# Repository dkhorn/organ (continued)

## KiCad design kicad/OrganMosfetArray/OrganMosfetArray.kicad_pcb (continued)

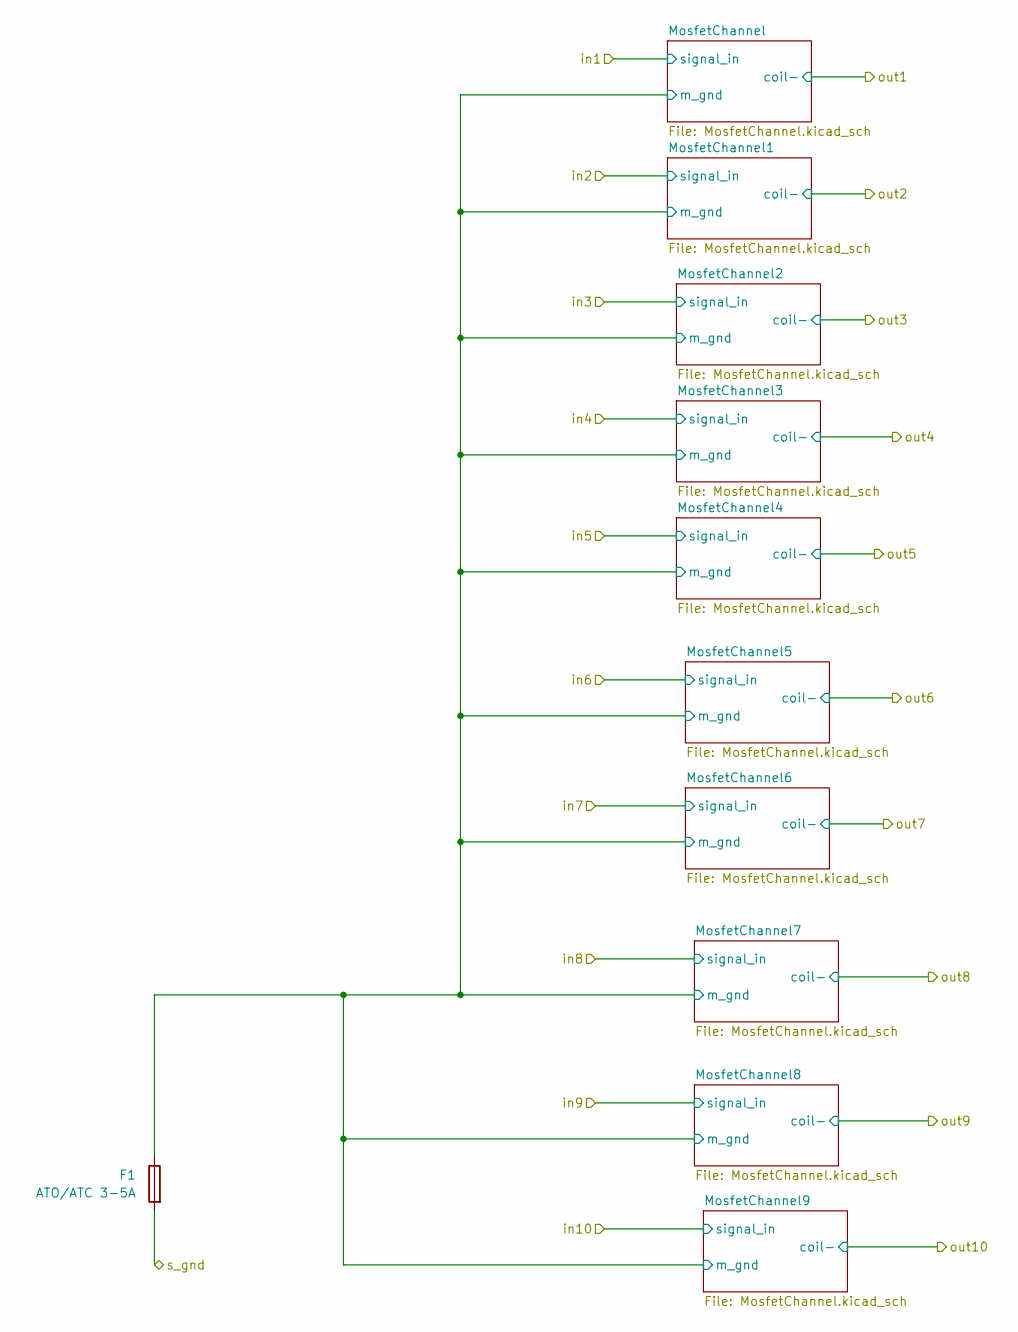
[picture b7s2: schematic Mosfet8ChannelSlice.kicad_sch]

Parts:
F1: ATO/ATC 3-5A; AliExpressFuseHolder

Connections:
/Mosfet8ChannelSlice/MosfetChannel/m_gnd: F1.1; also elsewhere on the board
GND: F1.2; also elsewhere on the board

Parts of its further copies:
F2, F3, F4, F5: ATO/ATC 3-5A; AliExpressFuseHolder

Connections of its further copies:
/Mosfet8ChannelSlice1/MosfetChannel/m_gnd: F2.1; also elsewhere on the board
/Mosfet8ChannelSlice2/MosfetChannel/m_gnd: F3.1; also elsewhere on the board
/Mosfet8ChannelSlice3/MosfetChannel/m_gnd: F4.1; also elsewhere on the board
/Mosfet8ChannelSlice4/MosfetChannel/m_gnd: F5.1; also elsewhere on the board
GND: F2.2, F3.2, F4.2, F5.2; also elsewhere on the board

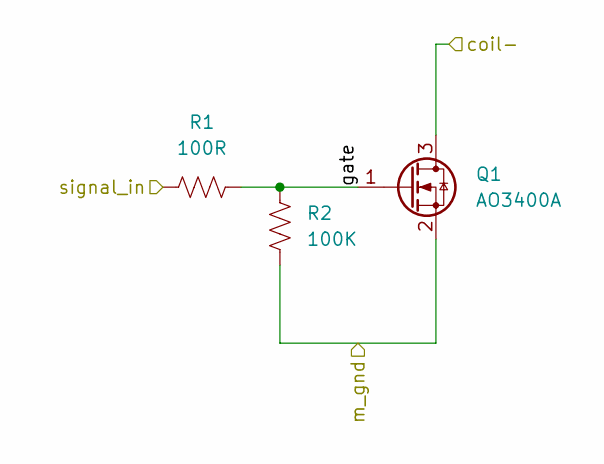
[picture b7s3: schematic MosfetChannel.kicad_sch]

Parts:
Q1: AO3400A; SOT-23
R1: 100R; R_0603_1608Metric
R2: 100K; R_0603_1608Metric

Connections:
/Mosfet8ChannelSlice/MosfetChannel/gate: Q1.1 (G), R1.2, R2.1
/Mosfet8ChannelSlice/MosfetChannel/m_gnd: Q1.2 (S), R2.2; also elsewhere on the board
/Mosfet8ChannelSlice/in1: R1.1; also elsewhere on the board
/Mosfet8ChannelSlice/out1: Q1.3 (D); also elsewhere on the board

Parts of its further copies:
Q2, Q3, Q4, Q5, Q6, Q7, Q8, Q9, Q10, Q11, Q12, Q13, Q14, Q15, Q16, Q17, Q18, Q19, Q20, Q21, Q22, Q23, Q24, Q25, Q26, Q27, Q28, Q29, Q30, Q31, Q32, Q33, Q34, Q35, Q36, Q37, Q38, Q39, Q40, Q41, Q42, Q43, Q44, Q45, Q46, Q47, Q48, Q49, Q50: AO3400A; SOT-23
R3, R5, R7, R9, R11, R13, R15, R17, R19, R21, R23, R25, R27, R29, R31, R33, R35, R37, R39, R41, R43, R45, R47, R49, R51, R53, R55, R57, R59, R61, R63, R65, R67, R69, R71, R73, R75, R77, R79, R81, R83, R85, R87, R89, R91, R93, R95, R97, R99: 100R; R_0603_1608Metric
R4, R6, R8, R10, R12, R14, R16, R18, R20, R22, R24, R26, R28, R30, R32, R34, R36, R38, R40, R42, R44, R46, R48, R50, R52, R54, R56, R58, R60, R62, R64, R66, R68, R70, R72, R74, R76, R78, R80, R82, R84, R86, R88, R90, R92, R94, R96, R98, R100: 100K; R_0603_1608Metric

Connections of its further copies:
/Mosfet8ChannelSlice1/MosfetChannel1/gate: Q11.1 (G), R21.2, R22.1
/Mosfet8ChannelSlice1/MosfetChannel2/gate: Q10.1 (G), R19.2, R20.1
/Mosfet8ChannelSlice1/MosfetChannel3/gate: Q9.1 (G), R17.2, R18.1
/Mosfet8ChannelSlice1/MosfetChannel4/gate: Q14.1 (G), R27.2, R28.1
/Mosfet8ChannelSlice1/MosfetChannel5/gate: Q12.1 (G), R23.2, R24.1
/Mosfet8ChannelSlice1/MosfetChannel6/gate: Q15.1 (G), R29.2, R30.1
/Mosfet8ChannelSlice1/MosfetChannel7/gate: Q16.1 (G), R31.2, R32.1
/Mosfet8ChannelSlice1/MosfetChannel8/gate: Q17.1 (G), R33.2, R34.1
/Mosfet8ChannelSlice1/MosfetChannel9/gate: Q18.1 (G), R35.2, R36.1
/Mosfet8ChannelSlice1/MosfetChannel/gate: Q13.1 (G), R25.2, R26.1
/Mosfet8ChannelSlice1/MosfetChannel/m_gnd: Q9.2 (S), Q10.2 (S), Q11.2 (S), Q12.2 (S), Q13.2 (S), Q14.2 (S), Q15.2 (S), Q16.2 (S), Q17.2 (S), Q18.2 (S), R18.2, R20.2, R22.2, R24.2, R26.2, R28.2, R30.2, R32.2, R34.2, R36.2; also elsewhere on the board
/Mosfet8ChannelSlice1/in1: R25.1; also elsewhere on the board
/Mosfet8ChannelSlice1/in2: R21.1; also elsewhere on the board
/Mosfet8ChannelSlice1/in3: R19.1; also elsewhere on the board
/Mosfet8ChannelSlice1/in4: R17.1; also elsewhere on the board
/Mosfet8ChannelSlice1/in5: R27.1; also elsewhere on the board
/Mosfet8ChannelSlice1/in6: R23.1; also elsewhere on the board
/Mosfet8ChannelSlice1/in7: R29.1; also elsewhere on the board
/Mosfet8ChannelSlice1/in8: R31.1; also elsewhere on the board
/Mosfet8ChannelSlice1/in9: R33.1; also elsewhere on the board
/Mosfet8ChannelSlice1/in10: R35.1; also elsewhere on the board
/Mosfet8ChannelSlice1/out1: Q13.3 (D); also elsewhere on the board
/Mosfet8ChannelSlice1/out2: Q11.3 (D); also elsewhere on the board
/Mosfet8ChannelSlice1/out3: Q10.3 (D); also elsewhere on the board
/Mosfet8ChannelSlice1/out4: Q9.3 (D); also elsewhere on the board
/Mosfet8ChannelSlice1/out5: Q14.3 (D); also elsewhere on the board
/Mosfet8ChannelSlice1/out6: Q12.3 (D); also elsewhere on the board
/Mosfet8ChannelSlice1/out7: Q15.3 (D); also elsewhere on the board
/Mosfet8ChannelSlice1/out8: Q16.3 (D); also elsewhere on the board
/Mosfet8ChannelSlice1/out9: Q17.3 (D); also elsewhere on the board
/Mosfet8ChannelSlice1/out10: Q18.3 (D); also elsewhere on the board
/Mosfet8ChannelSlice2/MosfetChannel1/gate: Q21.1 (G), R41.2, R42.1
/Mosfet8ChannelSlice2/MosfetChannel2/gate: Q20.1 (G), R39.2, R40.1
/Mosfet8ChannelSlice2/MosfetChannel3/gate: Q19.1 (G), R37.2, R38.1
/Mosfet8ChannelSlice2/MosfetChannel4/gate: Q24.1 (G), R47.2, R48.1
/Mosfet8ChannelSlice2/MosfetChannel5/gate: Q22.1 (G), R43.2, R44.1
/Mosfet8ChannelSlice2/MosfetChannel6/gate: Q25.1 (G), R49.2, R50.1
/Mosfet8ChannelSlice2/MosfetChannel7/gate: Q26.1 (G), R51.2, R52.1
/Mosfet8ChannelSlice2/MosfetChannel8/gate: Q27.1 (G), R53.2, R54.1
/Mosfet8ChannelSlice2/MosfetChannel9/gate: Q28.1 (G), R55.2, R56.1
/Mosfet8ChannelSlice2/MosfetChannel/gate: Q23.1 (G), R45.2, R46.1
/Mosfet8ChannelSlice2/MosfetChannel/m_gnd: Q19.2 (S), Q20.2 (S), Q21.2 (S), Q22.2 (S), Q23.2 (S), Q24.2 (S), Q25.2 (S), Q26.2 (S), Q27.2 (S), Q28.2 (S), R38.2, R40.2, R42.2, R44.2, R46.2, R48.2, R50.2, R52.2, R54.2, R56.2; also elsewhere on the board
/Mosfet8ChannelSlice2/in1: R45.1; also elsewhere on the board
/Mosfet8ChannelSlice2/in2: R41.1; also elsewhere on the board
/Mosfet8ChannelSlice2/in3: R39.1; also elsewhere on the board
/Mosfet8ChannelSlice2/in4: R37.1; also elsewhere on the board
/Mosfet8ChannelSlice2/in5: R47.1; also elsewhere on the board
/Mosfet8ChannelSlice2/in6: R43.1; also elsewhere on the board
/Mosfet8ChannelSlice2/in7: R49.1; also elsewhere on the board
/Mosfet8ChannelSlice2/in8: R51.1; also elsewhere on the board
/Mosfet8ChannelSlice2/in9: R53.1; also elsewhere on the board
/Mosfet8ChannelSlice2/in10: R55.1; also elsewhere on the board
/Mosfet8ChannelSlice2/out1: Q23.3 (D); also elsewhere on the board
/Mosfet8ChannelSlice2/out2: Q21.3 (D); also elsewhere on the board
/Mosfet8ChannelSlice2/out3: Q20.3 (D); also elsewhere on the board
/Mosfet8ChannelSlice2/out4: Q19.3 (D); also elsewhere on the board
/Mosfet8ChannelSlice2/out5: Q24.3 (D); also elsewhere on the board
/Mosfet8ChannelSlice2/out6: Q22.3 (D); also elsewhere on the board
/Mosfet8ChannelSlice2/out7: Q25.3 (D); also elsewhere on the board
/Mosfet8ChannelSlice2/out8: Q26.3 (D); also elsewhere on the board
/Mosfet8ChannelSlice2/out9: Q27.3 (D); also elsewhere on the board
/Mosfet8ChannelSlice2/out10: Q28.3 (D); also elsewhere on the board
/Mosfet8ChannelSlice3/MosfetChannel1/gate: Q31.1 (G), R61.2, R62.1
/Mosfet8ChannelSlice3/MosfetChannel2/gate: Q30.1 (G), R59.2, R60.1
/Mosfet8ChannelSlice3/MosfetChannel3/gate: Q29.1 (G), R57.2, R58.1
/Mosfet8ChannelSlice3/MosfetChannel4/gate: Q34.1 (G), R67.2, R68.1
/Mosfet8ChannelSlice3/MosfetChannel5/gate: Q32.1 (G), R63.2, R64.1
/Mosfet8ChannelSlice3/MosfetChannel6/gate: Q35.1 (G), R69.2, R70.1
/Mosfet8ChannelSlice3/MosfetChannel7/gate: Q36.1 (G), R71.2, R72.1
/Mosfet8ChannelSlice3/MosfetChannel8/gate: Q37.1 (G), R73.2, R74.1
/Mosfet8ChannelSlice3/MosfetChannel9/gate: Q38.1 (G), R75.2, R76.1
/Mosfet8ChannelSlice3/MosfetChannel/gate: Q33.1 (G), R65.2, R66.1
/Mosfet8ChannelSlice3/MosfetChannel/m_gnd: Q29.2 (S), Q30.2 (S), Q31.2 (S), Q32.2 (S), Q33.2 (S), Q34.2 (S), Q35.2 (S), Q36.2 (S), Q37.2 (S), Q38.2 (S), R58.2, R60.2, R62.2, R64.2, R66.2, R68.2, R70.2, R72.2, R74.2, R76.2; also elsewhere on the board
/Mosfet8ChannelSlice3/in1: R65.1; also elsewhere on the board
/Mosfet8ChannelSlice3/in2: R61.1; also elsewhere on the board
/Mosfet8ChannelSlice3/in3: R59.1; also elsewhere on the board
/Mosfet8ChannelSlice3/in4: R57.1; also elsewhere on the board
/Mosfet8ChannelSlice3/in5: R67.1; also elsewhere on the board
/Mosfet8ChannelSlice3/in6: R63.1; also elsewhere on the board
/Mosfet8ChannelSlice3/in7: R69.1; also elsewhere on the board
/Mosfet8ChannelSlice3/in8: R71.1; also elsewhere on the board
/Mosfet8ChannelSlice3/in9: R73.1; also elsewhere on the board
/Mosfet8ChannelSlice3/in10: R75.1; also elsewhere on the board
/Mosfet8ChannelSlice3/out1: Q33.3 (D); also elsewhere on the board
/Mosfet8ChannelSlice3/out2: Q31.3 (D); also elsewhere on the board
/Mosfet8ChannelSlice3/out3: Q30.3 (D); also elsewhere on the board
/Mosfet8ChannelSlice3/out4: Q29.3 (D); also elsewhere on the board
/Mosfet8ChannelSlice3/out5: Q34.3 (D); also elsewhere on the board
/Mosfet8ChannelSlice3/out6: Q32.3 (D); also elsewhere on the board
/Mosfet8ChannelSlice3/out7: Q35.3 (D); also elsewhere on the board
/Mosfet8ChannelSlice3/out8: Q36.3 (D); also elsewhere on the board
/Mosfet8ChannelSlice3/out9: Q37.3 (D); also elsewhere on the board
/Mosfet8ChannelSlice3/out10: Q38.3 (D); also elsewhere on the board
/Mosfet8ChannelSlice4/MosfetChannel1/gate: Q41.1 (G), R81.2, R82.1
/Mosfet8ChannelSlice4/MosfetChannel2/gate: Q40.1 (G), R79.2, R80.1
/Mosfet8ChannelSlice4/MosfetChannel3/gate: Q39.1 (G), R77.2, R78.1
/Mosfet8ChannelSlice4/MosfetChannel4/gate: Q44.1 (G), R87.2, R88.1
/Mosfet8ChannelSlice4/MosfetChannel5/gate: Q42.1 (G), R83.2, R84.1
/Mosfet8ChannelSlice4/MosfetChannel6/gate: Q45.1 (G), R89.2, R90.1
/Mosfet8ChannelSlice4/MosfetChannel7/gate: Q46.1 (G), R91.2, R92.1
/Mosfet8ChannelSlice4/MosfetChannel8/gate: Q47.1 (G), R93.2, R94.1
/Mosfet8ChannelSlice4/MosfetChannel9/gate: Q48.1 (G), R95.2, R96.1
/Mosfet8ChannelSlice4/MosfetChannel/gate: Q43.1 (G), R85.2, R86.1
/Mosfet8ChannelSlice4/MosfetChannel/m_gnd: Q39.2 (S), Q40.2 (S), Q41.2 (S), Q42.2 (S), Q43.2 (S), Q44.2 (S), Q45.2 (S), Q46.2 (S), Q47.2 (S), Q48.2 (S), R78.2, R80.2, R82.2, R84.2, R86.2, R88.2, R90.2, R92.2, R94.2, R96.2; also elsewhere on the board
/Mosfet8ChannelSlice4/in1: R85.1; also elsewhere on the board
/Mosfet8ChannelSlice4/in2: R81.1; also elsewhere on the board
/Mosfet8ChannelSlice4/in3: R79.1; also elsewhere on the board
/Mosfet8ChannelSlice4/in4: R77.1; also elsewhere on the board
/Mosfet8ChannelSlice4/in5: R87.1; also elsewhere on the board
/Mosfet8ChannelSlice4/in6: R83.1; also elsewhere on the board
/Mosfet8ChannelSlice4/in7: R89.1; also elsewhere on the board
/Mosfet8ChannelSlice4/in8: R91.1; also elsewhere on the board
/Mosfet8ChannelSlice4/in9: R93.1; also elsewhere on the board
/Mosfet8ChannelSlice4/in10: R95.1; also elsewhere on the board
/Mosfet8ChannelSlice4/out1: Q43.3 (D); also elsewhere on the board
/Mosfet8ChannelSlice4/out2: Q41.3 (D); also elsewhere on the board
/Mosfet8ChannelSlice4/out3: Q40.3 (D); also elsewhere on the board
/Mosfet8ChannelSlice4/out4: Q39.3 (D); also elsewhere on the board
/Mosfet8ChannelSlice4/out5: Q44.3 (D); also elsewhere on the board
/Mosfet8ChannelSlice4/out6: Q42.3 (D); also elsewhere on the board
/Mosfet8ChannelSlice4/out7: Q45.3 (D); also elsewhere on the board
/Mosfet8ChannelSlice4/out8: Q46.3 (D); also elsewhere on the board
/Mosfet8ChannelSlice4/out9: Q47.3 (D); also elsewhere on the board
/Mosfet8ChannelSlice4/out10: Q48.3 (D); also elsewhere on the board
/Mosfet8ChannelSlice/MosfetChannel1/gate: Q2.1 (G), R3.2, R4.1
/Mosfet8ChannelSlice/MosfetChannel2/gate: Q3.1 (G), R5.2, R6.1
/Mosfet8ChannelSlice/MosfetChannel3/gate: Q4.1 (G), R7.2, R8.1
/Mosfet8ChannelSlice/MosfetChannel4/gate: Q5.1 (G), R9.2, R10.1
/Mosfet8ChannelSlice/MosfetChannel5/gate: Q6.1 (G), R11.2, R12.1
/Mosfet8ChannelSlice/MosfetChannel6/gate: Q7.1 (G), R13.2, R14.1
/Mosfet8ChannelSlice/MosfetChannel7/gate: Q8.1 (G), R15.2, R16.1
/Mosfet8ChannelSlice/MosfetChannel8/gate: Q49.1 (G), R97.2, R98.1
/Mosfet8ChannelSlice/MosfetChannel9/gate: Q50.1 (G), R99.2, R100.1
/Mosfet8ChannelSlice/MosfetChannel/m_gnd: Q2.2 (S), Q3.2 (S), Q4.2 (S), Q5.2 (S), Q6.2 (S), Q7.2 (S), Q8.2 (S), Q49.2 (S), Q50.2 (S), R4.2, R6.2, R8.2, R10.2, R12.2, R14.2, R16.2, R98.2, R100.2; also elsewhere on the board
/Mosfet8ChannelSlice/in2: R3.1; also elsewhere on the board
/Mosfet8ChannelSlice/in3: R5.1; also elsewhere on the board
/Mosfet8ChannelSlice/in4: R7.1; also elsewhere on the board
/Mosfet8ChannelSlice/in5: R9.1; also elsewhere on the board
/Mosfet8ChannelSlice/in6: R11.1; also elsewhere on the board
/Mosfet8ChannelSlice/in7: R13.1; also elsewhere on the board
/Mosfet8ChannelSlice/in8: R15.1; also elsewhere on the board
/Mosfet8ChannelSlice/in9: R97.1; also elsewhere on the board
/Mosfet8ChannelSlice/in10: R99.1; also elsewhere on the board
/Mosfet8ChannelSlice/out2: Q2.3 (D); also elsewhere on the board
/Mosfet8ChannelSlice/out3: Q3.3 (D); also elsewhere on the board
/Mosfet8ChannelSlice/out4: Q4.3 (D); also elsewhere on the board
/Mosfet8ChannelSlice/out5: Q5.3 (D); also elsewhere on the board
/Mosfet8ChannelSlice/out6: Q6.3 (D); also elsewhere on the board
/Mosfet8ChannelSlice/out7: Q7.3 (D); also elsewhere on the board
/Mosfet8ChannelSlice/out8: Q8.3 (D); also elsewhere on the board
/Mosfet8ChannelSlice/out9: Q49.3 (D); also elsewhere on the board
/Mosfet8ChannelSlice/out10: Q50.3 (D); also elsewhere on the board

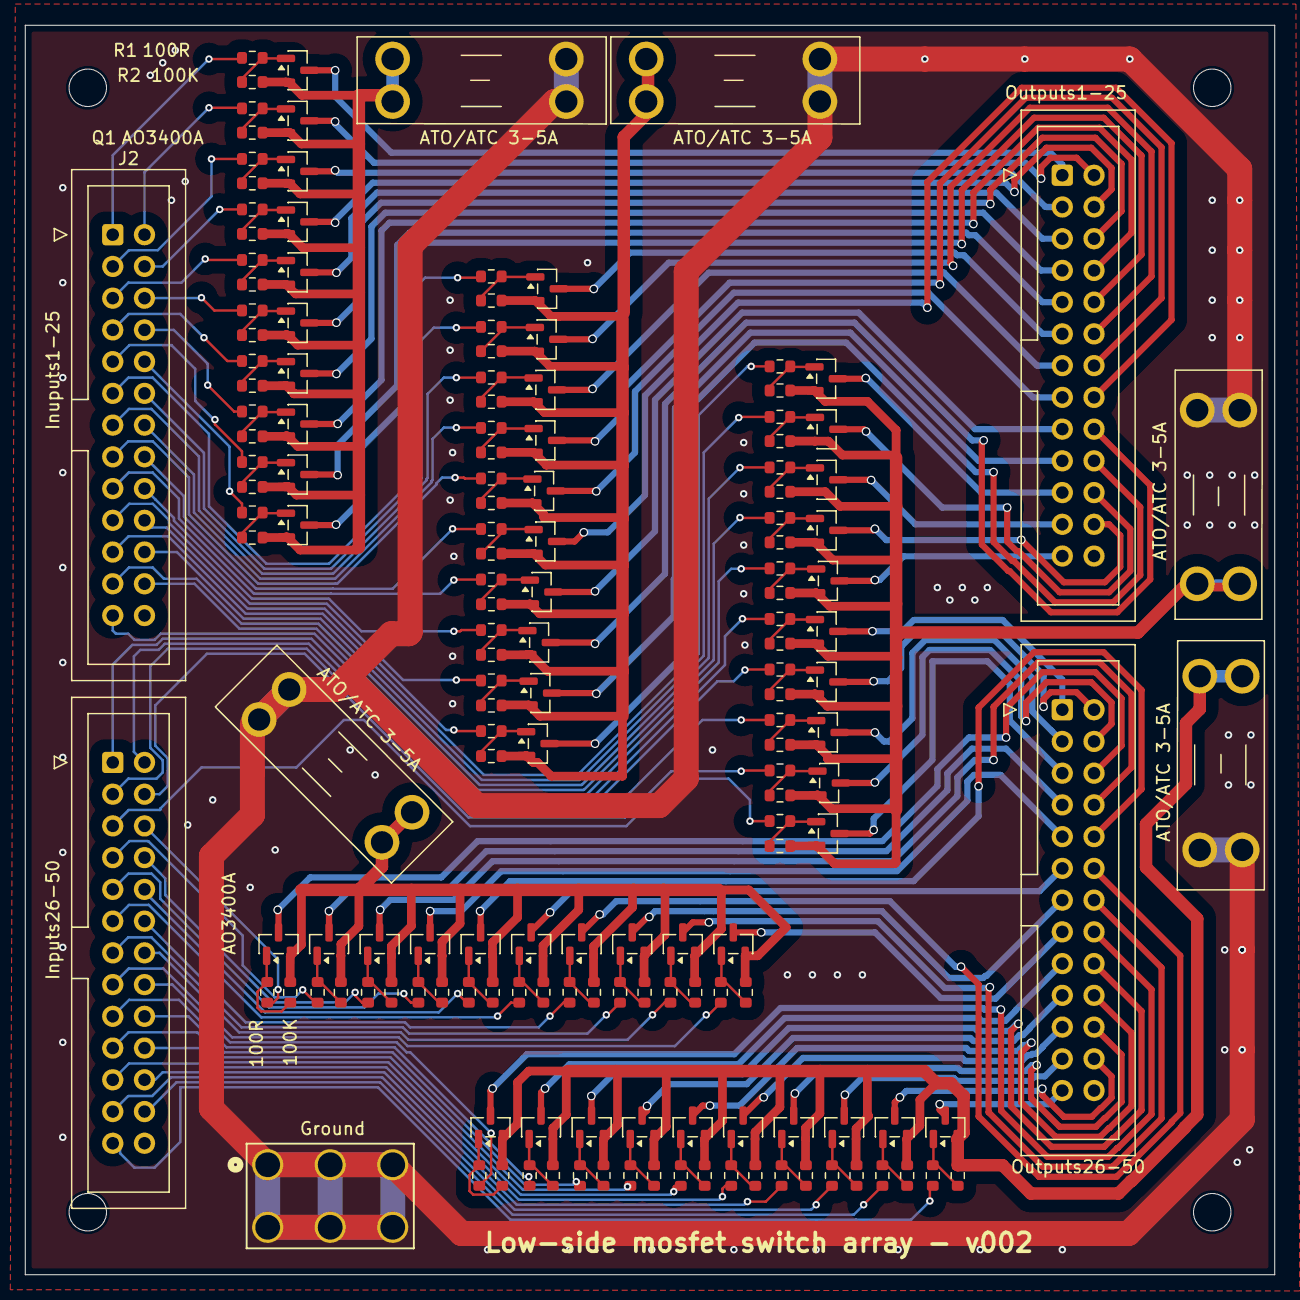
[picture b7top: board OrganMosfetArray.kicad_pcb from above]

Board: 2 copper layers, 100.0 x 100.0 mm, 160 parts (0 on the bottom side), 156 nets.

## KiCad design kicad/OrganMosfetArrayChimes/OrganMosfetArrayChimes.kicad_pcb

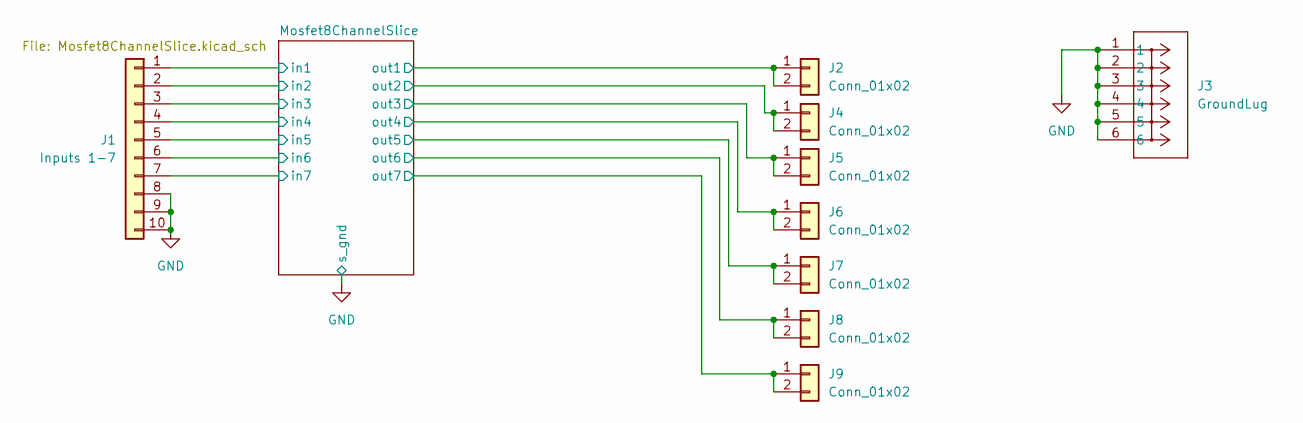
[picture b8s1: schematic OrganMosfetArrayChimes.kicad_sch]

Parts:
J1: Inputs 1-7; IDC-Header_2x05_P2.54mm_Vertical
J2, J4, J5, J6, J7, J8, J9: Conn_01x02; PinHeader_1x02_P2.54mm_Vertical
J3: GroundLug; CONN_8199_KEY

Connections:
/Mosfet8ChannelSlice/in1: J1.1; also elsewhere on the board
/Mosfet8ChannelSlice/in2: J1.2; also elsewhere on the board
/Mosfet8ChannelSlice/in3: J1.3; also elsewhere on the board
/Mosfet8ChannelSlice/in4: J1.4; also elsewhere on the board
/Mosfet8ChannelSlice/in5: J1.5; also elsewhere on the board
/Mosfet8ChannelSlice/in6: J1.6; also elsewhere on the board
/Mosfet8ChannelSlice/in7: J1.7; also elsewhere on the board
/Mosfet8ChannelSlice/out1: J2.1, J2.2; also elsewhere on the board
/Mosfet8ChannelSlice/out2: J4.1, J4.2; also elsewhere on the board
/Mosfet8ChannelSlice/out3: J5.1, J5.2; also elsewhere on the board
/Mosfet8ChannelSlice/out4: J6.1, J6.2; also elsewhere on the board
/Mosfet8ChannelSlice/out5: J7.1, J7.2; also elsewhere on the board
/Mosfet8ChannelSlice/out6: J8.1, J8.2; also elsewhere on the board
/Mosfet8ChannelSlice/out7: J9.1, J9.2; also elsewhere on the board
GND: J1.8, J1.9, J1.10, J3.1, J3.2, J3.3, J3.4, J3.5, J3.6; also elsewhere on the board

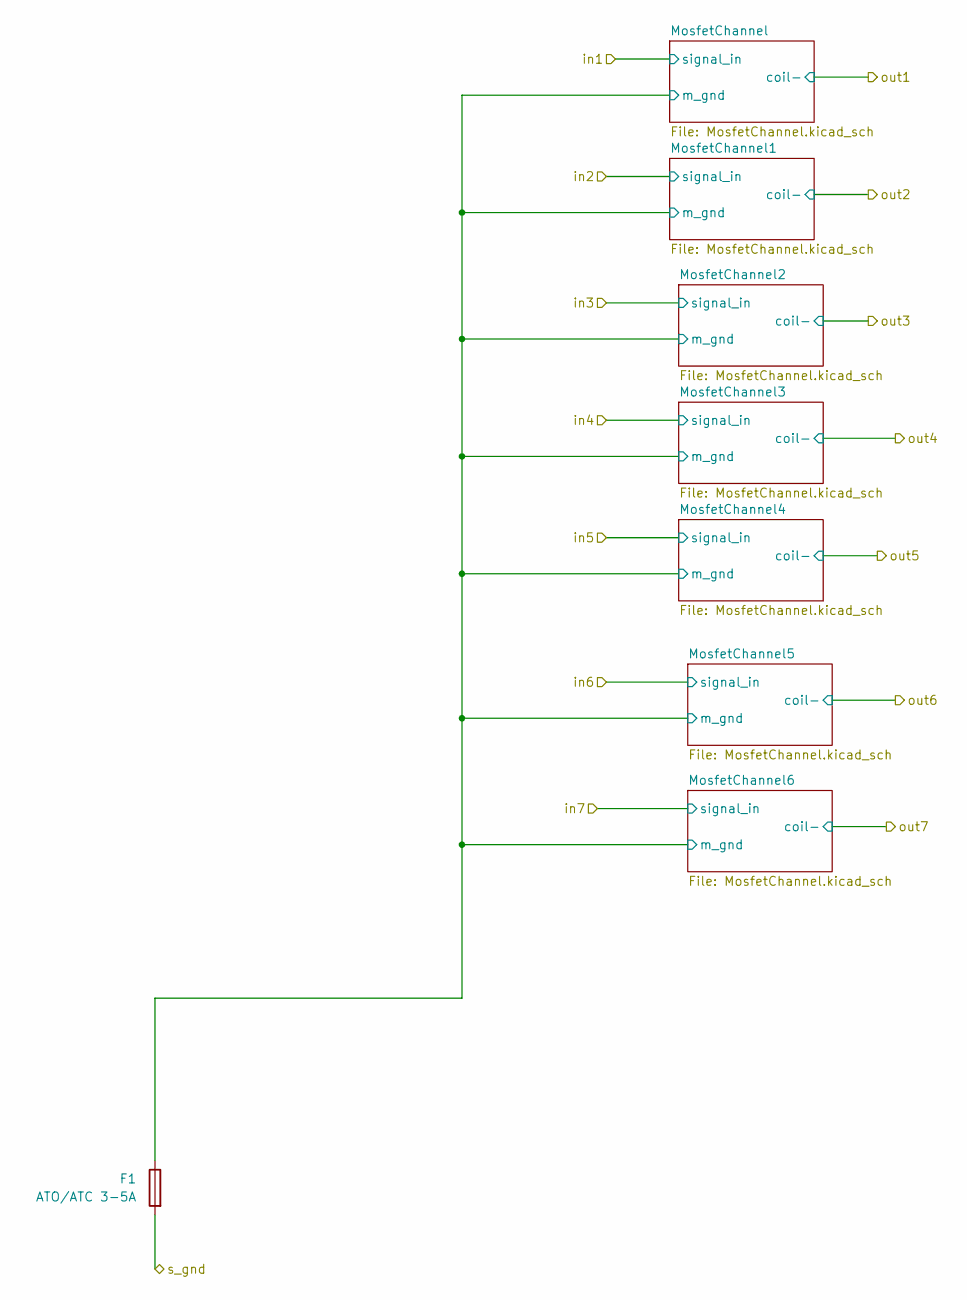
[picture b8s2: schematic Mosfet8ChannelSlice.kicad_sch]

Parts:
F1: ATO/ATC 3-5A; AliExpressFuseHolder

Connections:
/Mosfet8ChannelSlice/MosfetChannel/m_gnd: F1.1; also elsewhere on the board
GND: F1.2; also elsewhere on the board

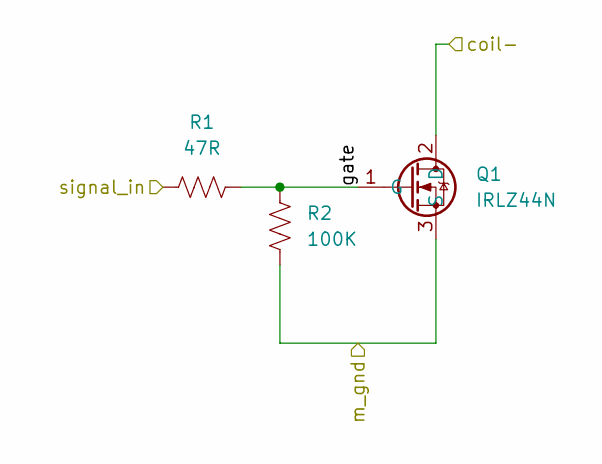
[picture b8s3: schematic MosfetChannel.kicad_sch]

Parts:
Q1: IRLZ44N; TO-220-3_Vertical
R1: 47R; R_Axial_DIN0207_L6.3mm_D2.5mm_P2.54mm_Vertical
R2: 100K; R_Axial_DIN0207_L6.3mm_D2.5mm_P2.54mm_Vertical

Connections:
/Mosfet8ChannelSlice/MosfetChannel/gate: Q1.1 (G), R1.2, R2.1
/Mosfet8ChannelSlice/MosfetChannel/m_gnd: Q1.3 (S), R2.2; also elsewhere on the board
/Mosfet8ChannelSlice/in1: R1.1; also elsewhere on the board
/Mosfet8ChannelSlice/out1: Q1.2 (D); also elsewhere on the board

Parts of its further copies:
Q2, Q3, Q4, Q5, Q6, Q7: IRLZ44N; TO-220-3_Vertical
R3, R5, R7, R9, R11, R13: 47R; R_Axial_DIN0207_L6.3mm_D2.5mm_P2.54mm_Vertical
R4, R6, R8, R10, R12, R14: 100K; R_Axial_DIN0207_L6.3mm_D2.5mm_P2.54mm_Vertical

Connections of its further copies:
/Mosfet8ChannelSlice/MosfetChannel1/gate: Q2.1 (G), R3.2, R4.1
/Mosfet8ChannelSlice/MosfetChannel2/gate: Q3.1 (G), R5.2, R6.1
/Mosfet8ChannelSlice/MosfetChannel3/gate: Q4.1 (G), R7.2, R8.1
/Mosfet8ChannelSlice/MosfetChannel4/gate: Q5.1 (G), R9.2, R10.1
/Mosfet8ChannelSlice/MosfetChannel5/gate: Q6.1 (G), R11.2, R12.1
/Mosfet8ChannelSlice/MosfetChannel6/gate: Q7.1 (G), R13.2, R14.1
/Mosfet8ChannelSlice/MosfetChannel/m_gnd: Q2.3 (S), Q3.3 (S), Q4.3 (S), Q5.3 (S), Q6.3 (S), Q7.3 (S), R4.2, R6.2, R8.2, R10.2, R12.2, R14.2; also elsewhere on the board
/Mosfet8ChannelSlice/in2: R3.1; also elsewhere on the board
/Mosfet8ChannelSlice/in3: R5.1; also elsewhere on the board
/Mosfet8ChannelSlice/in4: R7.1; also elsewhere on the board
/Mosfet8ChannelSlice/in5: R9.1; also elsewhere on the board
/Mosfet8ChannelSlice/in6: R11.1; also elsewhere on the board
/Mosfet8ChannelSlice/in7: R13.1; also elsewhere on the board
/Mosfet8ChannelSlice/out2: Q2.2 (D); also elsewhere on the board
/Mosfet8ChannelSlice/out3: Q3.2 (D); also elsewhere on the board
/Mosfet8ChannelSlice/out4: Q4.2 (D); also elsewhere on the board
/Mosfet8ChannelSlice/out5: Q5.2 (D); also elsewhere on the board
/Mosfet8ChannelSlice/out6: Q6.2 (D); also elsewhere on the board
/Mosfet8ChannelSlice/out7: Q7.2 (D); also elsewhere on the board

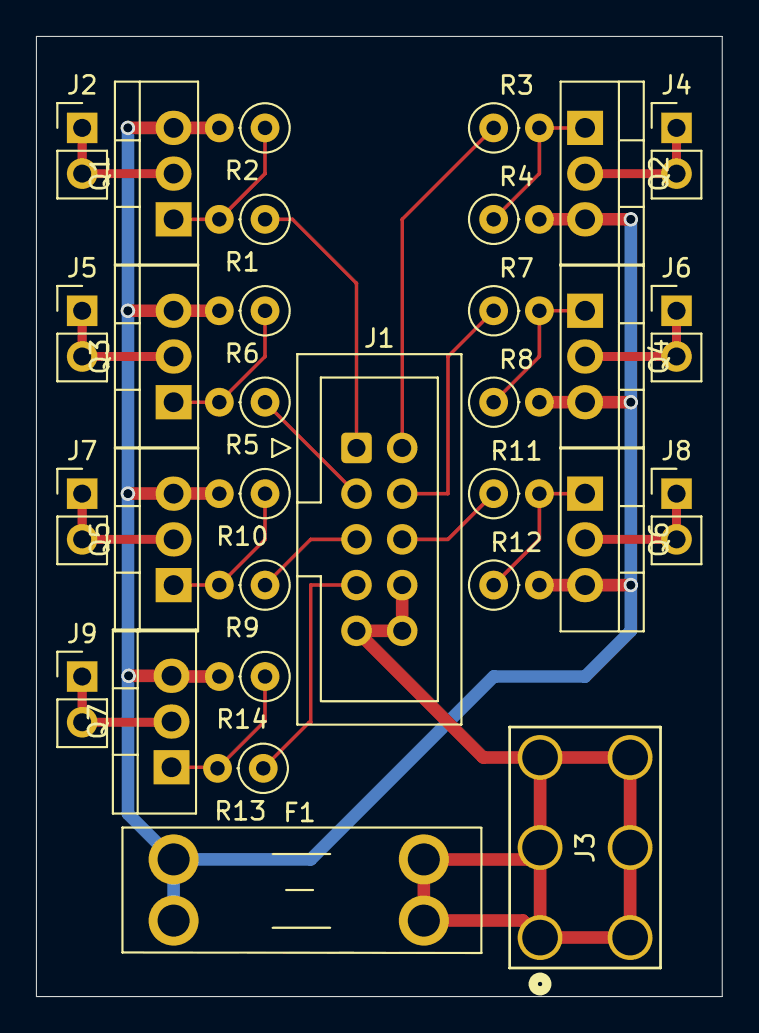
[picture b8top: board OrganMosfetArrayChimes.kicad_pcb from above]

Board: 2 copper layers, 38.1 x 53.3 mm, 31 parts (0 on the bottom side), 23 nets.

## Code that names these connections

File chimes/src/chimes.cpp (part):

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
static Chan CH[21] = {
  // 12 x MCPWM  (UNIT0 & UNIT1)
  {ChType::MCP, MCPWM_UNIT_0, MCPWM_TIMER_0, MCPWM_OPR_A}, // 0 -> GPIO4
  {ChType::MCP, MCPWM_UNIT_0, MCPWM_TIMER_0, MCPWM_OPR_B}, // 1 -> GPIO5
  {ChType::MCP, MCPWM_UNIT_0, MCPWM_TIMER_1, MCPWM_OPR_A}, // 2 -> GPIO6
  {ChType::MCP, MCPWM_UNIT_0, MCPWM_TIMER_1, MCPWM_OPR_B}, // 3 -> GPIO7
  {ChType::MCP, MCPWM_UNIT_0, MCPWM_TIMER_2, MCPWM_OPR_A}, // 4 -> GPIO15
  {ChType::MCP, MCPWM_UNIT_0, MCPWM_TIMER_2, MCPWM_OPR_B}, // 5 -> GPIO16
  {ChType::MCP, MCPWM_UNIT_1, MCPWM_TIMER_0, MCPWM_OPR_A}, // 6 -> GPIO17
  {ChType::MCP, MCPWM_UNIT_1, MCPWM_TIMER_0, MCPWM_OPR_B}, // 7 -> GPIO18
  {ChType::MCP, MCPWM_UNIT_1, MCPWM_TIMER_1, MCPWM_OPR_A}, // 8 -> GPIO8
  {ChType::MCP, MCPWM_UNIT_1, MCPWM_TIMER_1, MCPWM_OPR_B}, // 9 -> GPIO3
  {ChType::MCP, MCPWM_UNIT_1, MCPWM_TIMER_2, MCPWM_OPR_A}, // 10 -> GPIO9
  {ChType::MCP, MCPWM_UNIT_1, MCPWM_TIMER_2, MCPWM_OPR_B}, // 11 -> GPIO10

  // 9 x LEDC (pins: 11,12,13,14,1,2,37,36,35)
  {ChType::LEDC, MCPWM_UNIT_MAX, MCPWM_TIMER_MAX, MCPWM_OPR_MAX,  0, 11}, // 12 -> 11
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
static void initMCPWM() {
  // Route GPIOs
  // UNIT0: timers 0..2 -> GPIO12/13,14/15,16/17
  mcpwm_gpio_init(MCPWM_UNIT_0, MCPWM0A, MCP_GPIO[0]);
  mcpwm_gpio_init(MCPWM_UNIT_0, MCPWM0B, MCP_GPIO[1]);
  mcpwm_gpio_init(MCPWM_UNIT_0, MCPWM1A, MCP_GPIO[2]);
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  mcpwm_gpio_init(MCPWM_UNIT_0, MCPWM2A, MCP_GPIO[4]);
  mcpwm_gpio_init(MCPWM_UNIT_0, MCPWM2B, MCP_GPIO[5]);

  // UNIT1: timers 0..2 -> GPIO4/5,6/7,8/9
  mcpwm_gpio_init(MCPWM_UNIT_1, MCPWM0A, MCP_GPIO[6]);
  mcpwm_gpio_init(MCPWM_UNIT_1, MCPWM0B, MCP_GPIO[7]);
  mcpwm_gpio_init(MCPWM_UNIT_1, MCPWM1A, MCP_GPIO[8]);
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
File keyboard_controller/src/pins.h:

#ifndef PINS_H
#define PINS_H

// ---------- I2C bus (MCP23017 key scanner) ----------
const int PIN_I2C_SDA = 4;   // GPIO4  – SDA (4.7 kΩ pull-up fitted)
const int PIN_I2C_SCL = 5;   // GPIO5  – SCL (4.7 kΩ pull-up fitted)
const int PIN_I2C_INT = 6;   // GPIO6  – shared active-low INT from all MCP23017s (4.7 kΩ pull-up fitted)

// ---------- CAN bus (TWAI) ----------
const int PIN_CAN_RX = 1;    // GPIO1, physical pin 41
const int PIN_CAN_TX = 2;    // GPIO2, physical pin 40

// Keyboard scanner parameters (base note and CAN channel) are now determined
// at runtime by the hardware_id stored in NVS.  See key_scanner_get_hardware_id()
// and key_scanner_get_can_channel().

#endif

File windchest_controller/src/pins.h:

#ifndef PINS_H
#define PINS_H
// ---------- Pin assignments (ESP32-S3-DevKitC-1) ----------

// SPI shift-register bus
const int PIN_CLR_N  = 10;  // /SRCLR  - GPIO10, physical pin 16
const int PIN_OE_N   = 11;  // /OE     - GPIO11, physical pin 17
const int PIN_SCK    = 12;  // SCK     - GPIO12, physical pin 18
const int PIN_MOSI   = 13;  // MOSI    - GPIO13, physical pin 19
const int PIN_LATCH  = 14;  // LATCH   - GPIO14, physical pin 20

// MIDI serial input (UART2)
const int PIN_MIDI_RX = 17; // GPIO17, physical pin 10

#endif

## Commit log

2025-11-19 Initial commit of chimes esp32 project
2025-11-23 MVP of chimes controller
2025-11-23 Adding circuit projects
2025-11-26 Adding hardware test program
2025-12-01 Refactoring workspaces
2025-12-09 Many new chimes features
2025-12-11 Revert "Refactoring workspaces"
    This reverts commit a825f6877cdec550308f1665d89193b6d4ae9f92.
2025-12-11 Quality-of-life updates, etc
2025-12-15 Adding kicad stuff for MCU board
2025-12-16 Finishing MCU board and lots of chimes updates
2025-12-22 Adding keyswitch breakout and inventory list
2025-12-26 Maturing chimes firmware, etc
2026-01-07 Finalized v001 of MCU board for production
2026-01-11 Finishing keyswitch breakout board
2026-02-09 Adding keyswitch breakout system, and some tools
2026-02-09 Adding unified soundboard schematic - unfinished
2026-02-11 Adding some custom components that some of the kicad things depend on
2026-02-11 Something...
2026-02-16 Updating hardwaretest to be windchest really, adding some 3d models for things
2026-03-05 Adding punch
2026-03-05 Adding a bunch of documentation, etc
2026-03-05 Finalized unified soundboard driver for production, adding some models
2026-03-09 Updating 3d models
2026-03-09 layout changes
2026-03-09 Adding images of casavant in place, and updating 3d models
2026-03-10 Adding printable scale model
2026-03-10 Updating layouts
2026-03-16 Updating ranks, stops, 3d models
2026-03-17 Adding a bunch of new firmware
2026-03-19 Updating models
2026-03-19 Windchest controller feature complete
2026-03-23 Adding valve count spreadsheet
2026-03-23 Adding another packing option
2026-03-25 Adding architecture document
2026-03-26 Adding new models and detailed dimensions
2026-03-27 Refining pipes modeling
2026-03-30 Updating bourdon layout
2026-04-03 Adding keyswitch shims for printing
